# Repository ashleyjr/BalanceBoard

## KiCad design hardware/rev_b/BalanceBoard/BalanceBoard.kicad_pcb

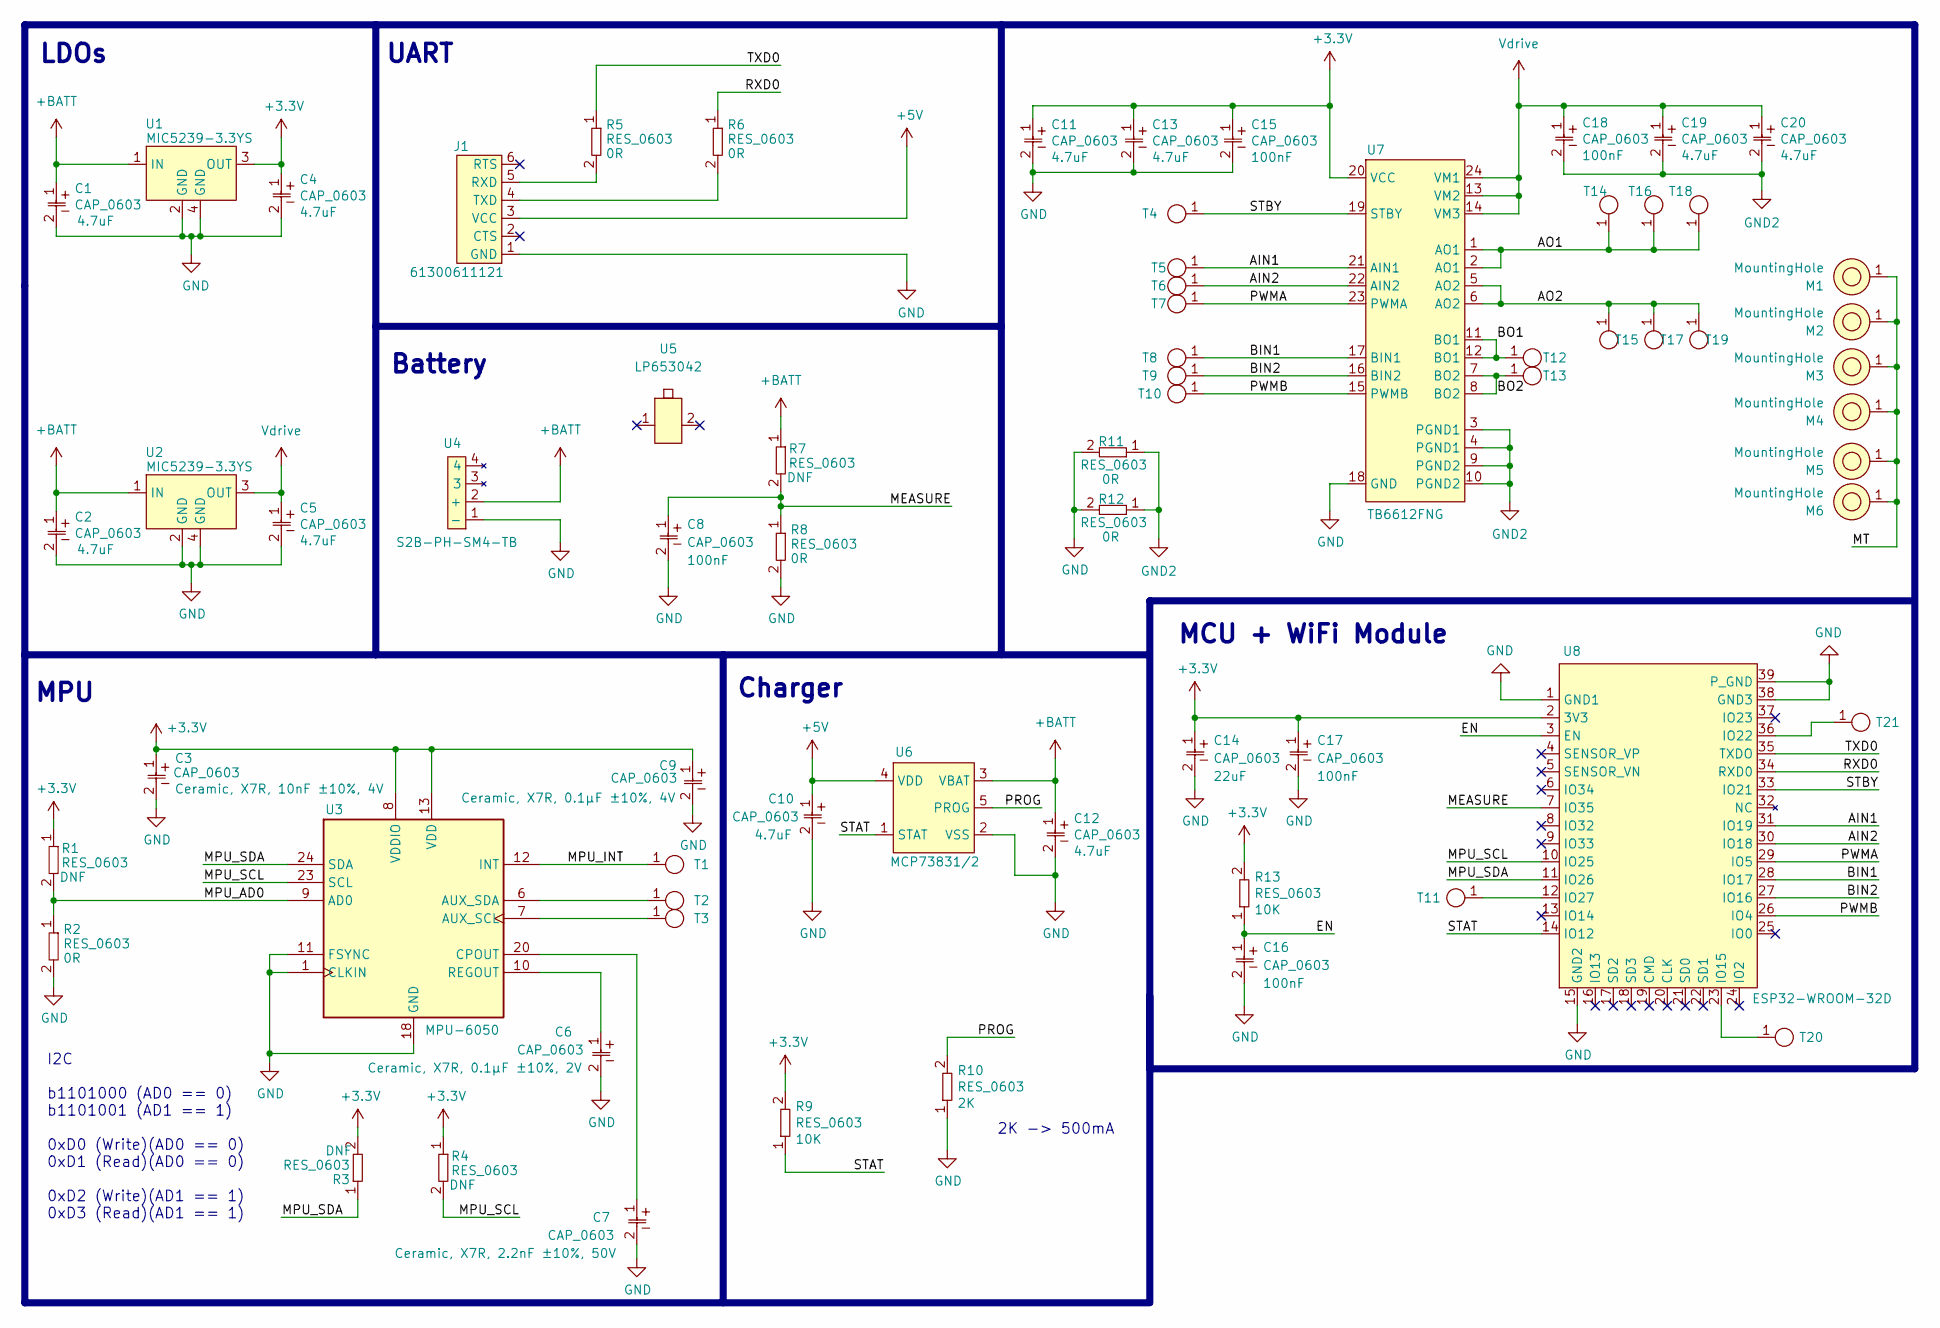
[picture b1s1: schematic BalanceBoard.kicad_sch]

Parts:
C1, C2, C3, C4, C5, C6, C7, C8, C9, C10, C11, C12, C13, C14, C15, C16, C17, C18, C19, C20: CAP_0603; 0603
J1: 61300611121
M1, M2, M3, M4, M5, M6: MountingHole
R1, R2, R3, R4, R5, R6, R7, R8, R9, R10, R11, R12, R13: RES_0603; 0603
T1, T2, T3, T4, T5, T6, T7, T8, T9, T10, T11, T12, T13, T14, T15, T16, T17, T18, T19, T20, T21: TestPoints; TestPoint
U1, U2: MIC5239-3.3YS
U3: MPU-6050; InvenSense_QFN-24_4x4mm_P0.5mm
U4: S2B-PH-SM4-TB
U5: LP653042
U6: MCP73831/2; MCP738312
U7: TB6612FNG
U8: ESP32-WROOM-32D

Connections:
+3V3: C3.1, C4.1, C9.1, C11.1, C13.1, C14.1, C15.1, C17.1, R1.1, R3.2, R4.1, R9.2, R13.2, U1.3 (OUT), U3.8 (VDDIO), U3.13 (VDD), U7.20 (VCC), U8.2 (3V3)
+5V: C10.1, J1.3 (VCC), U6.4 (VDD)
+BATT: C1.1, C2.1, C12.1, R7.1, U1.1 (IN), U2.1 (IN), U4.2 (+), U6.3 (VBAT)
/AIN1: T5.1, U7.21 (AIN1), U8.31 (IO19)
/AIN2: T6.1, U7.22 (AIN2), U8.30 (IO18)
/AO1: T14.1, T16.1, T18.1, U7.1 (AO1), U7.2 (AO1)
/AO2: T15.1, T17.1, T19.1, U7.5 (AO2), U7.6 (AO2)
/BIN1: T8.1, U7.17 (BIN1), U8.28 (IO17)
/BIN2: T9.1, U7.16 (BIN2), U8.27 (IO16)
/BO1: T12.1, U7.11 (BO1), U7.12 (BO1)
/BO2: T13.1, U7.7 (BO2), U7.8 (BO2)
/EN: C16.1, R13.1, U8.3 (EN)
/MEASURE: C8.1, R7.2, R8.1, U8.7 (IO35)
/MPU_AD0: R1.2, R2.1, U3.9 (AD0)
/MPU_INT: T1.1, U3.12 (INT)
/MPU_SCL: R4.2, U3.23 (SCL), U8.10 (IO25)
/MPU_SDA: R3.1, U3.24 (SDA), U8.11 (IO26)
/MT: M1.1, M2.1, M3.1, M4.1, M5.1, M6.1
/PROG: R10.2, U6.5 (PROG)
/PWMA: T7.1, U7.23 (PWMA), U8.29 (IO5)
/PWMB: T10.1, U7.15 (PWMB), U8.26 (IO4)
/RXD0: R6.1, U8.34 (RXD0)
/STAT: R9.1, U6.1 (STAT), U8.14 (IO12)
/STBY: T4.1, U7.19 (STBY), U8.33 (IO21)
/TXD0: R5.1, U8.35 (TXDO)
GND: C1.2, C2.2, C3.2, C4.2, C5.2, C6.2, C7.2, C8.2, C9.2, C10.2, C11.2, C12.2, C13.2, C14.2, C15.2, C16.2, C17.2, J1.1 (GND), R2.2, R8.2, R10.1, R11.2, R12.2, U1.2 (GND), U1.4 (GND), U2.2 (GND), U2.4 (GND), U3.1 (CLKIN), U3.11 (FSYNC), U3.18 (GND), U4.1 (-), U6.2 (VSS), U7.18 (GND), U8.1 (GND1), U8.15 (GND2), U8.38 (GND3), U8.39 (P_GND)
GND2: C18.2, C19.2, C20.2, R11.1, R12.1, U7.3 (PGND1), U7.4 (PGND1), U7.9 (PGND2), U7.10 (PGND2)
unnamed: C6.1, U3.10 (REGOUT)
unnamed: C7.1, U3.20 (CPOUT)
unnamed: J1.4 (TXD), R6.2
unnamed: J1.5 (RXD), R5.2
unnamed: T2.1, U3.6 (AUX_SDA)
unnamed: T3.1, U3.7 (AUX_SCL)
unnamed: T11.1, U8.12 (IO27)
unnamed: T20.1, U8.23 (IO15)
unnamed: T21.1, U8.36 (IO22)
Vdrive: C5.1, C18.1, C19.1, C20.1, U2.3 (OUT), U7.13 (VM2), U7.14 (VM3), U7.24 (VM1)

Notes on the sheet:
2K -> 500mA
LDOs
MCU + WiFi Module
Battery
I2C b1101000 (AD0 == 0) b1101001 (AD1 == 1) 0xD0 (Write)(AD0 == 0) 0xD1 (Read)(AD0 == 0) 0xD2 (Write)(AD1 == 1) 0xD3 (Read)(AD1 == 1)
MPU
UART
Charger

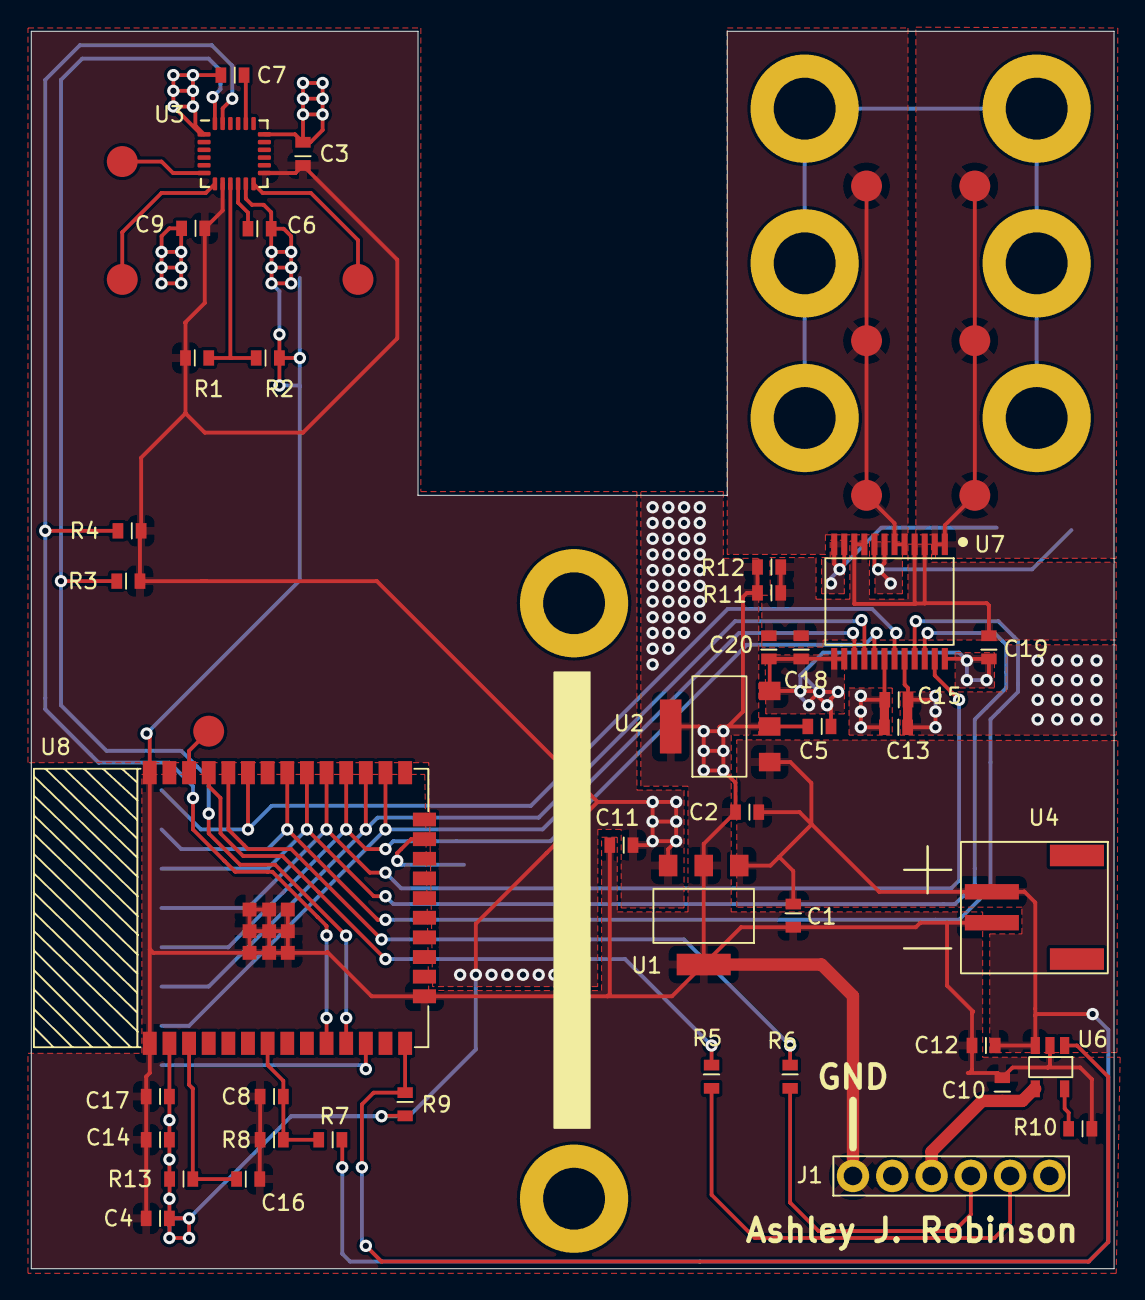
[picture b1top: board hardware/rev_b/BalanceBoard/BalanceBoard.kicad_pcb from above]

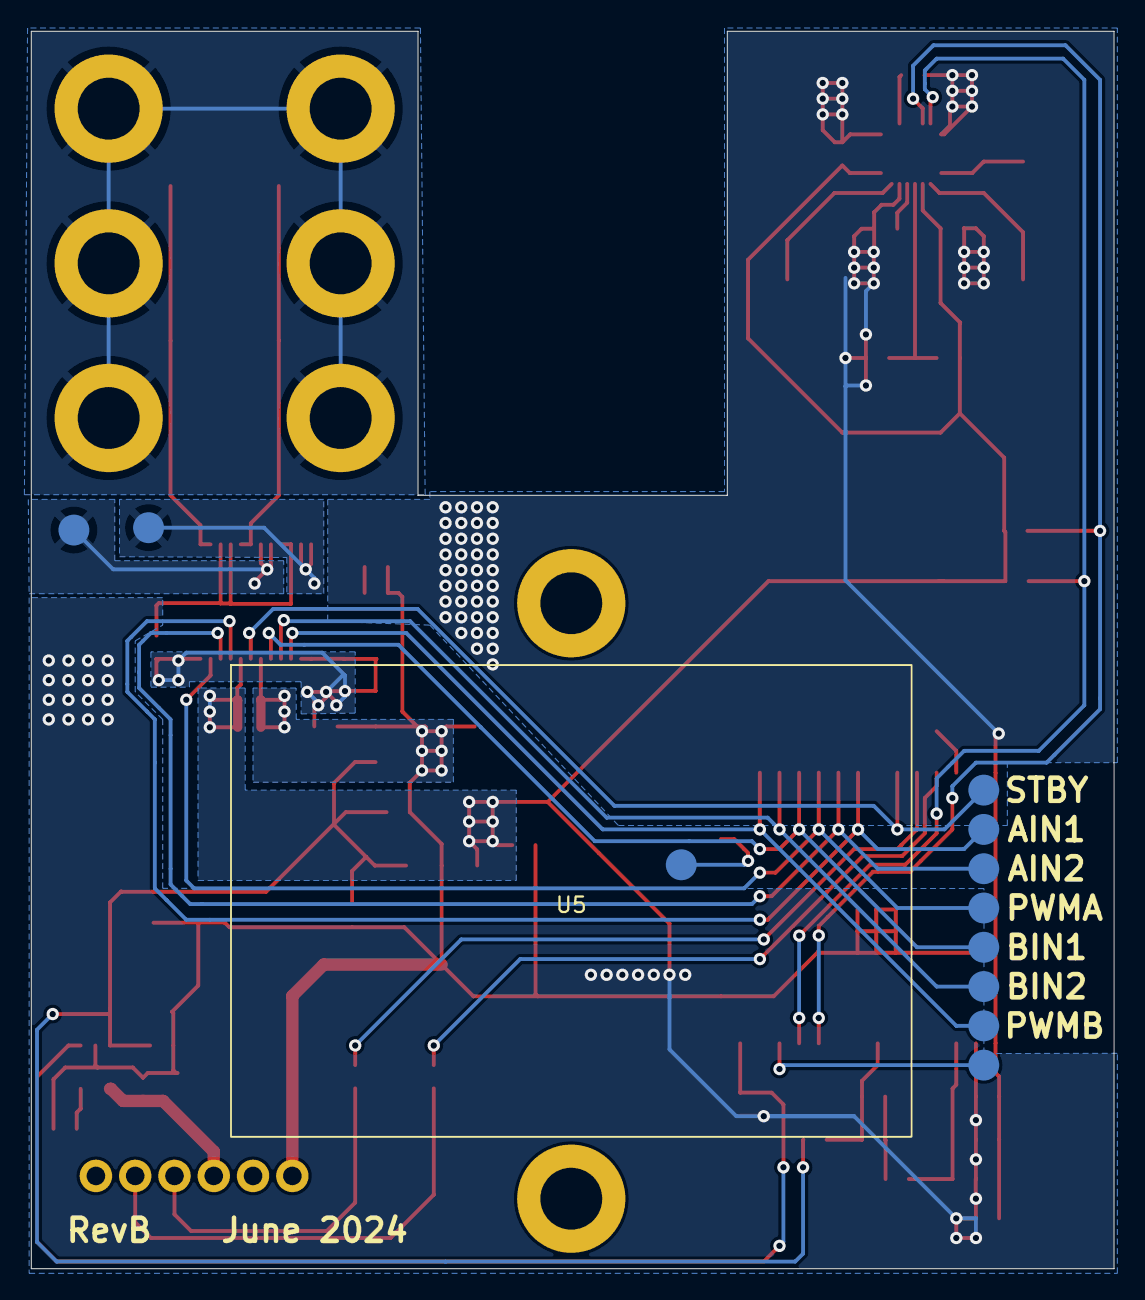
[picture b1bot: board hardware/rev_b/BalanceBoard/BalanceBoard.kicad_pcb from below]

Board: 2 copper layers, 70.0 x 80.0 mm, 69 parts (12 on the bottom side), 37 nets.

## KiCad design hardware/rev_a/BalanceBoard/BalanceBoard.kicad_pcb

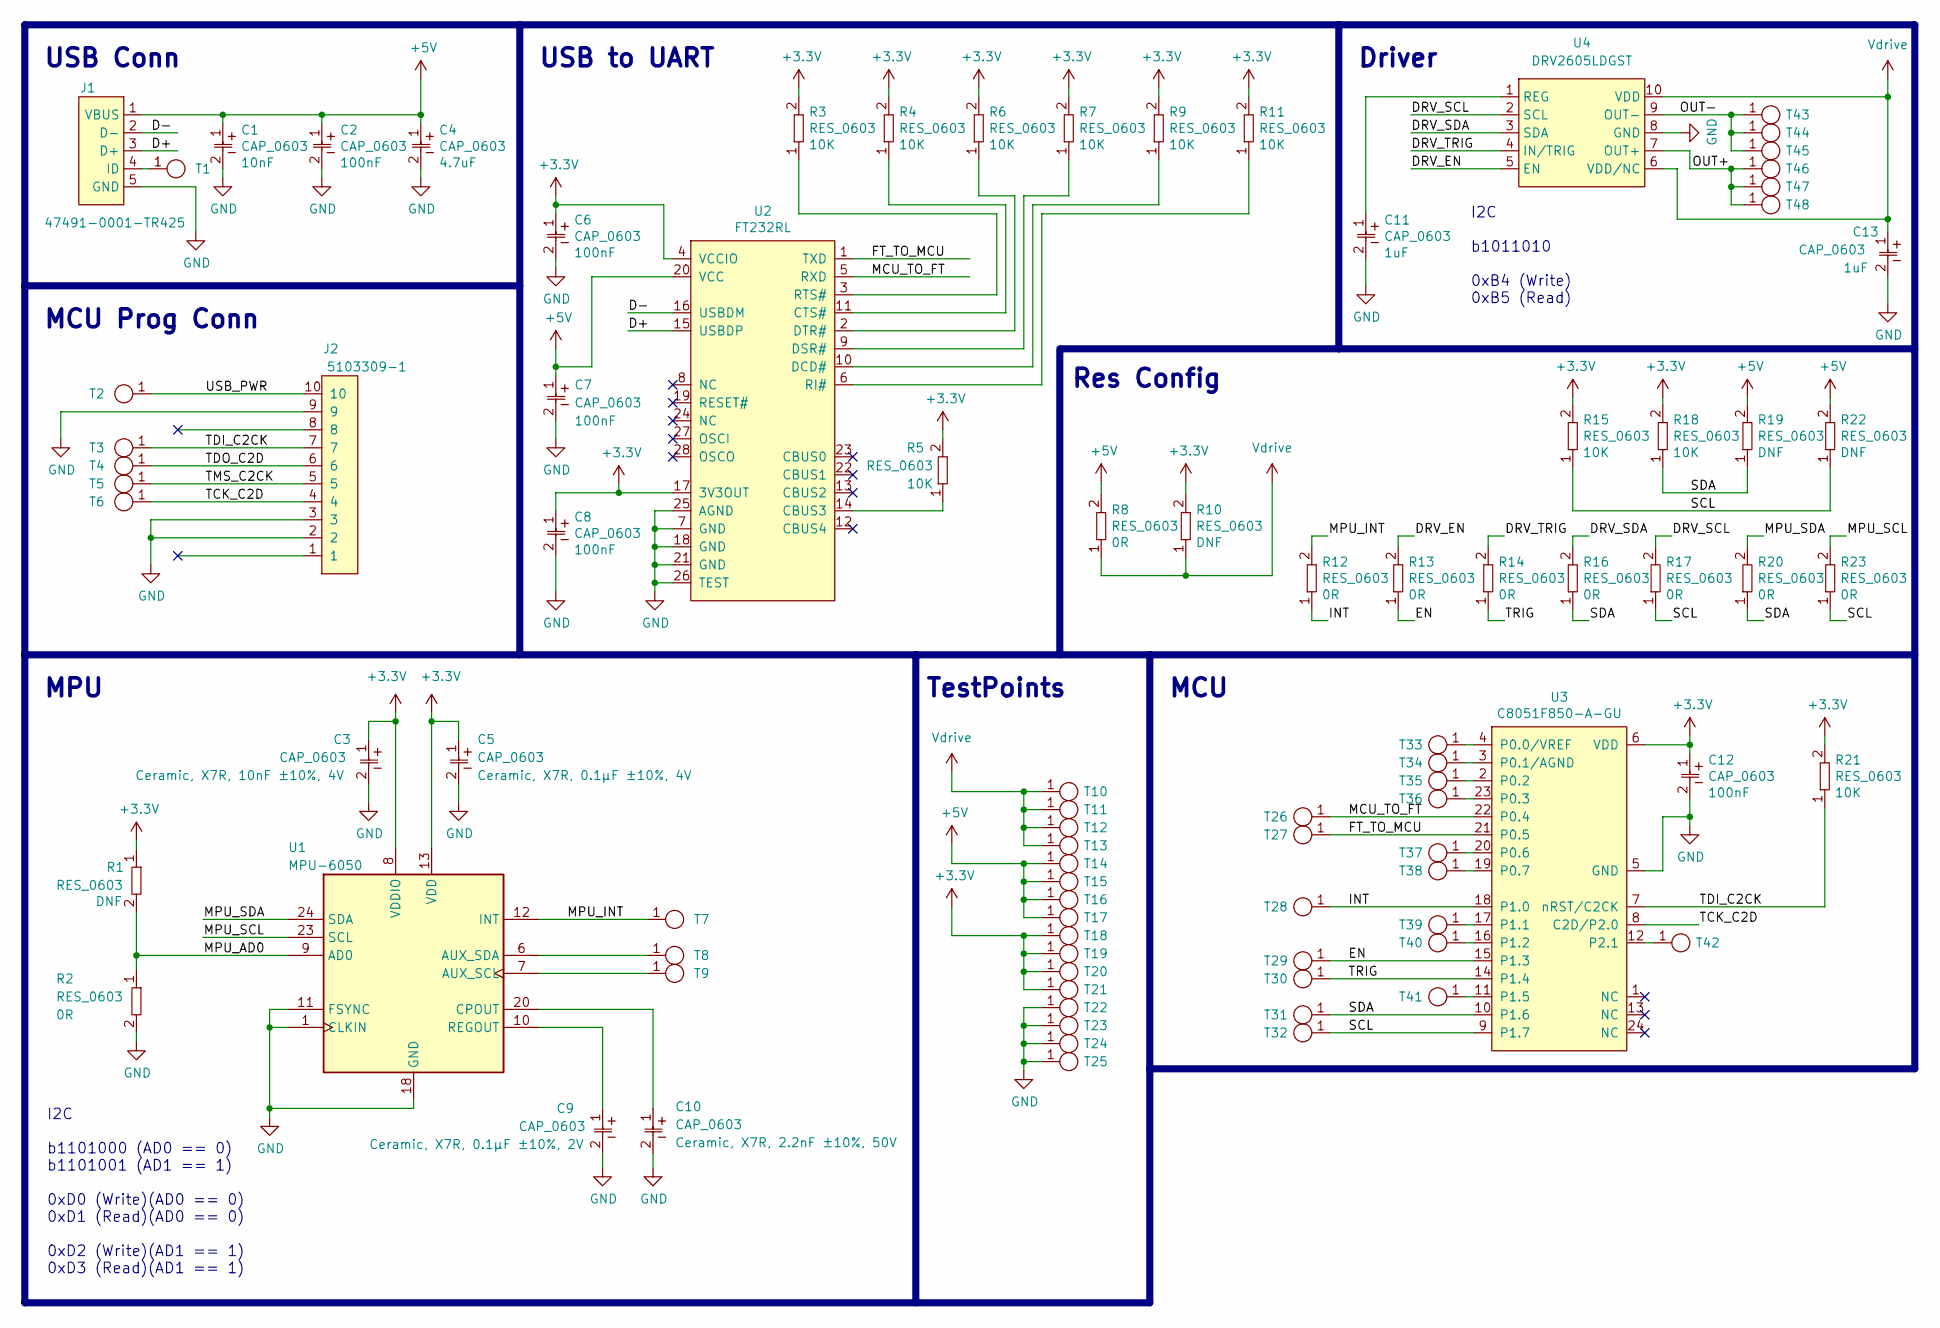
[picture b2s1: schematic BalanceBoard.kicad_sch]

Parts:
C1, C2, C3, C4, C5, C6, C7, C8, C9, C10, C11, C12, C13: CAP_0603; 0603
J1: 47491-0001-TR425
J2: 5103309-1
R1, R2, R3, R4, R5, R6, R7, R8, R9, R10, R11, R12, R13, R14, R15, R16, R17, R18, R19, R20, R21, R22, R23: RES_0603; 0603
T1, T2, T3, T4, T5, T6, T7, T8, T9, T10, T11, T12, T13, T14, T15, T16, T17, T18, T19, T20, T21, T22, T23, T24, T25, T26, T27, T28, T29, T30, T31, T32, T33, T34, T35, T36, T37, T38, T39, T40, T41, T42, T43, T44, T45, T46, T47, T48: TestPoints; TestPoint
U1: MPU-6050; InvenSense_QFN-24_4x4mm_P0.5mm
U2: FT232RL
U3: C8051F850-A-GU
U4: DRV2605LDGST

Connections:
+3V3: C3.1, C5.1, C6.1, C8.1, C12.1, R1.1, R3.2, R4.2, R5.2, R6.2, R7.2, R9.2, R10.2, R11.2, R15.2, R18.2, R21.2, T18.1, T19.1, T20.1, T21.1, U1.8 (VDDIO), U1.13 (VDD), U2.4 (VCCIO), U2.17 (3V3OUT), U3.6 (VDD)
+5V: C1.1, C2.1, C4.1, C7.1, J1.1 (VBUS), R8.2, R19.2, R22.2, T14.1, T15.1, T16.1, T17.1, U2.20 (VCC)
/D+: J1.3 (D+), U2.15 (USBDP)
/D-: J1.2 (D-), U2.16 (USBDM)
/DRV_EN: R13.2, U4.5 (EN)
/DRV_SCL: R17.2, U4.2 (SCL)
/DRV_SDA: R16.2, U4.3 (SDA)
/DRV_TRIG: R14.2, U4.4 (IN/TRIG)
/EN: R13.1, T29.1, U3.15 (P1.3)
/FT_TO_MCU: T27.1, U2.1 (TXD), U3.21 (P0.5)
/INT: R12.1, T28.1, U3.18 (P1.0)
/MCU_TO_FT: T26.1, U2.5 (RXD), U3.22 (P0.4)
/MPU_AD0: R1.2, R2.1, U1.9 (AD0)
/MPU_INT: R12.2, T7.1, U1.12 (INT)
/MPU_SCL: R23.2, U1.23 (SCL)
/MPU_SDA: R20.2, U1.24 (SDA)
/OUT+: T46.1, T47.1, T48.1, U4.7 (OUT+)
/OUT-: T43.1, T44.1, T45.1, U4.9 (OUT-)
/SCL: R15.1, R17.1, R22.1, R23.1, T32.1, U3.9 (P1.7)
/SDA: R16.1, R18.1, R19.1, R20.1, T31.1, U3.10 (P1.6)
/TCK_C2D: J2.4, T6.1, U3.8 (C2D/P2.0)
/TDI_C2CK: J2.7, R21.1, T3.1, U3.7 (nRST/C2CK)
/TDO_C2D: J2.6, T4.1
/TMS_C2CK: J2.5, T5.1
/TRIG: R14.1, T30.1, U3.14 (P1.4)
/USB_PWR: J2.10, T2.1
GND: C1.2, C2.2, C3.2, C4.2, C5.2, C6.2, C7.2, C8.2, C9.2, C10.2, C11.2, C12.2, C13.2, J1.5 (GND), J2.2, J2.3, J2.9, R2.2, T22.1, T23.1, T24.1, T25.1, U1.1 (CLKIN), U1.11 (FSYNC), U1.18 (GND), U2.7 (GND), U2.18 (GND), U2.21 (GND), U2.25 (AGND), U2.26 (TEST), U3.5 (GND), U4.8 (GND)
unnamed: C9.1, U1.10 (REGOUT)
unnamed: C10.1, U1.20 (CPOUT)
unnamed: C11.1, U4.1 (REG)
unnamed: J1.4 (ID), T1.1
unnamed: R3.1, U2.3 (RTS#)
unnamed: R4.1, U2.11 (CTS#)
unnamed: R5.1, U2.14 (CBUS3)
unnamed: R6.1, U2.2 (DTR#)
unnamed: R7.1, U2.9 (DSR#)
unnamed: R9.1, U2.10 (DCD#)
unnamed: R11.1, U2.6 (RI#)
unnamed: T8.1, U1.6 (AUX_SDA)
unnamed: T9.1, U1.7 (AUX_SCL)
unnamed: T33.1, U3.4 (P0.0/VREF)
unnamed: T34.1, U3.3 (P0.1/AGND)
unnamed: T35.1, U3.2 (P0.2)
unnamed: T36.1, U3.23 (P0.3)
unnamed: T37.1, U3.20 (P0.6)
unnamed: T38.1, U3.19 (P0.7)
unnamed: T39.1, U3.17 (P1.1)
unnamed: T40.1, U3.16 (P1.2)
unnamed: T41.1, U3.11 (P1.5)
unnamed: T42.1, U3.12 (P2.1)
Vdrive: C13.1, R8.1, R10.1, T10.1, T11.1, T12.1, T13.1, U4.6 (VDD/NC), U4.10 (VDD)

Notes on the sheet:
Driver
Res Config
I2C b1011010 0xB4 (Write) 0xB5 (Read)
MCU Prog Conn
I2C b1101000 (AD0 == 0) b1101001 (AD1 == 1) 0xD0 (Write)(AD0 == 0) 0xD1 (Read)(AD0 == 0) 0xD2 (Write)(AD1 == 1) 0xD3 (Read)(AD1 == 1)
MPU
TestPoints
MCU
USB to UART
USB Conn

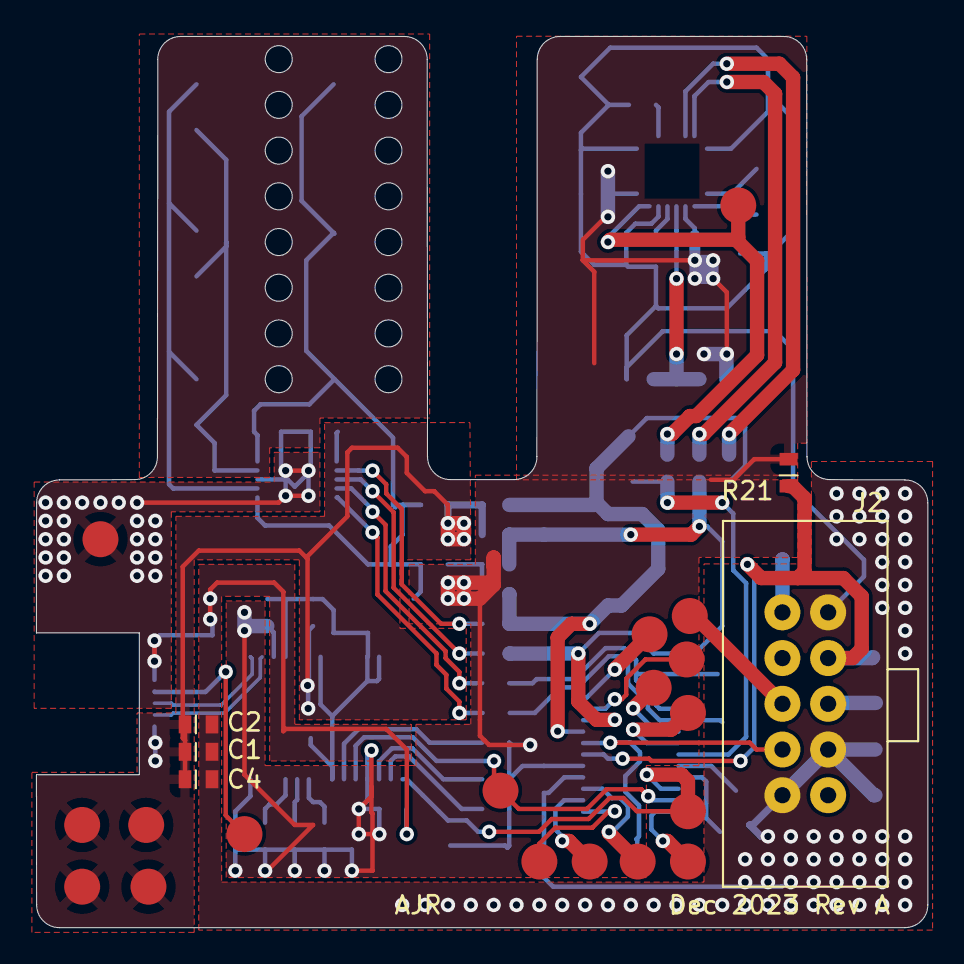
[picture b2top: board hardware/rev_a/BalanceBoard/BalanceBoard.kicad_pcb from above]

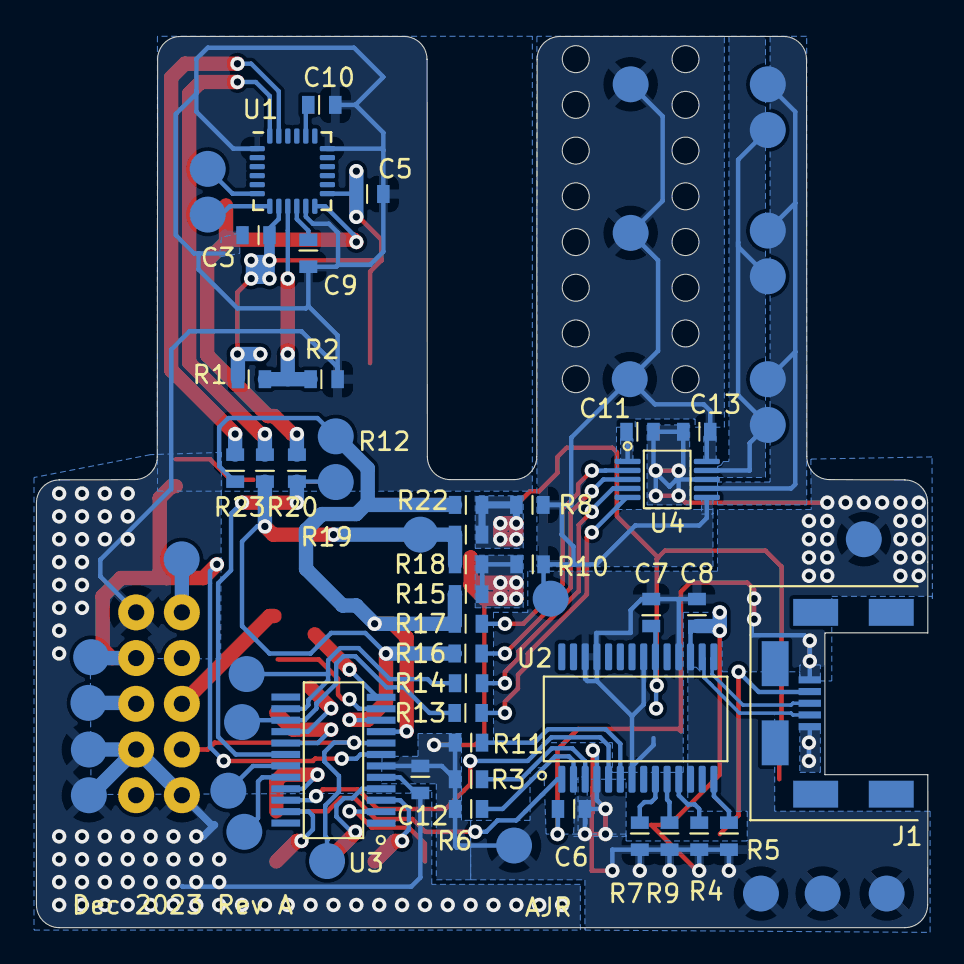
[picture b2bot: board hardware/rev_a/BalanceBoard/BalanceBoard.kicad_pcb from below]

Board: 2 copper layers, 49.5 x 49.5 mm, 90 parts (67 on the bottom side), 51 nets.

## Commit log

2023-11-22 start mcu sw
2023-11-22 makefile
2023-11-26 ignore
2023-11-26 hardware
2023-11-26 test
2023-11-26 tidy
2023-11-26 reset pcb
2023-11-27 update I2C SM
2023-11-28 change usb
2023-12-07 rev a fab out
2023-12-10 smbRead working
2023-12-14 tune ios
2023-12-14 add graph file
2023-12-15 graphs
2023-12-16 combine log and graph
2023-12-17 print outptu
2024-03-20 mv software to rev_a
2024-03-20 add esp
2024-03-20 add build scripts
2024-03-20 sdkconfig ignore
2024-03-20 script
2024-03-20 test script
2024-03-20 bw test
2024-03-21 add plotting example
2024-03-25 added i2c read
2024-03-25 remove readme
2024-03-27 timer test
2024-03-28 timer taking samples
2024-03-28 stream test
2024-04-07 add i2c plotting example
2024-04-09 added buffer
2024-04-10 plot of data working
2024-04-11 add PWM
2024-04-19 start rev b
2024-04-20 add batt + LDO
2024-05-16 start main proj
2024-05-16 rename
2024-05-17 started menu
2024-05-22 control LED
2024-05-23 more menu options
2024-05-24 motor A working
2024-05-24 Started mech
2024-05-28 gen constants for python
2024-05-28 bigger wheel
2024-06-03 working
2024-06-03 2 PWMs working
2024-06-04 Update schematic
2024-06-20 Rev B fab out
2024-07-18 work
2024-07-18 setup
2024-07-20 plot working
2024-07-20 teting motor
2024-07-20 token
2024-07-22 more sensor data
2024-08-10 add PID
2024-08-10 new data scheme works
2024-08-11 first working PID (wrong direction)
